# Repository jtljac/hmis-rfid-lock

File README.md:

# hmis-locks
A [PlatformIO](https://platformio.org/) program for a electronic locks that are unlocked using a Wiegand based RFID 
scanner and authorises users using a HMIS endpoint.

# Keypad support
Wiegand readers with keypads are supported. You can configure the valid keycode by setting the `enable_keypad_passcode`
option to a numeric string up to 8 numbers long.

When using the keypad, the '*' (star) button will clear (provided it maps to 0x0A), and the '#' (Hashtag) button will
submit (provided it maps to 0x0B).

# Setup
## Platform IO
This application uses [PlatformIO](https://platformio.org/) for dependency management and installation. Installation
instructions for your platform can be found [here](https://platformio.org/install/cli).

## Config
Configuration options have been exposed in [platformio.ini](/platformio.ini) under the `[base_config]` section.

The `WiFi` and `HMIS` options must be configured for your network and HMIS server. 

The `Unlock` and `Auth` options can be configured to suit your needs. 

The `Pins` options should be configured for your ESP, preferably in a separate section that inherits the `[base_config]` 
section (see the `[config_dfrobot_firebeetle2_esp32e]` section for an example of this).

The `Pin Inversions` options should be configured to match your circuit.

A preset environment has been provided for the [FireBeetle 2 ESP32-E](https://wiki.dfrobot.com/FireBeetle_Board_ESP32_E_SKU_DFR0654#target_5)
(my chosen ESP32), you will need to provide your own environment with it's required pin setup if you have a different
ESP32 (we welcome PRs for alternative setups).

## Installation
Run the following to build and upload the project to your ESP32:
```shell
# [your-env] should be one of the configured env sections in platformio.ini
pio run -t upload -e [your-env]
```

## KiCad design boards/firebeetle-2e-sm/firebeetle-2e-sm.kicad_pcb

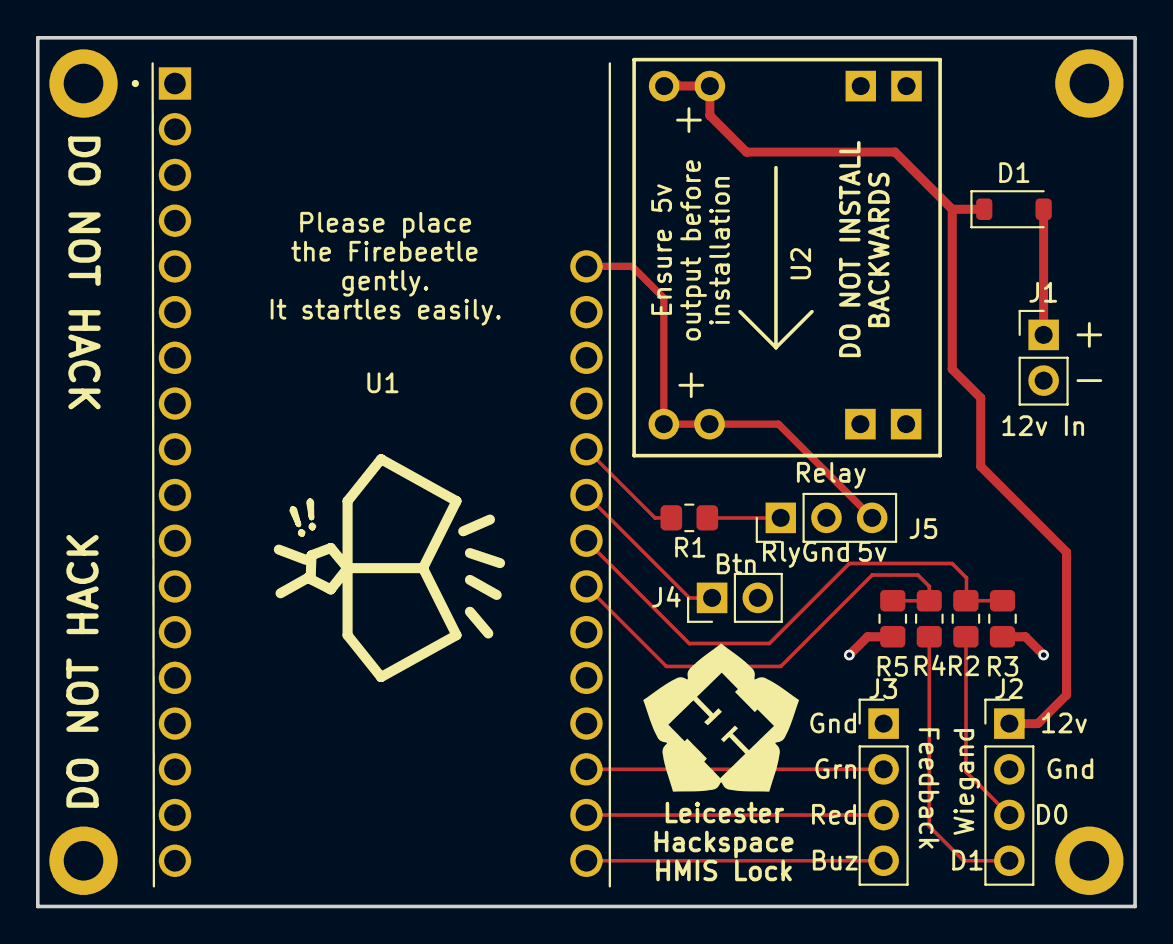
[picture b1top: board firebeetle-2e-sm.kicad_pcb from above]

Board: 2 copper layers, 61.0 x 48.3 mm, 17 parts (0 on the bottom side), 14 nets.

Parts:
D1: 1N5819; D_SOD-123
J1: Power In; PinHeader_1x02_P2.54mm_Vertical
J2: Wiegand; PinHeader_1x04_P2.54mm_Vertical
J3: Feedback; PinHeader_1x04_P2.54mm_Vertical
J4: Button; PinHeader_1x02_P2.54mm_Vertical
J5: Relay; PinHeader_1x03_P2.54mm_Vertical
M1, M2, M3, M4: MountingHole_2.2mm_M2_DIN965_Pad
R1: 5k1; R_0805_2012Metric_Pad1.20x1.40mm_HandSolder
R2, R4: 1k; R_0805_2012Metric_Pad1.20x1.40mm_HandSolder
R3, R5: 3.3k; R_0805_2012Metric_Pad1.20x1.40mm_HandSolder
U1: DFR0654; MODULE_DFR0654
U2: MP1584EN Module

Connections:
+5V: J5.3, U1.5 (VCC), U2.4 (VOut)
+12V: D1.1 (K), J2.1, U2.1 (VIn)
/Btn: J4.1, U1.15 (A4)
/Relay: R1.1, U1.21 (SDA)
/buz: J3.4, U1.17 (D10)
/d0: R2.1, R3.2, U1.35 (A3)
/d1: R4.1, R5.1, U1.34 (A2)
/grn: J3.2, U1.4 (D12)
/red: J3.3, U1.16 (D11)
GND: J1.2, J2.2, J3.1, J4.2, J5.2, M1.1, M2.1, M3.1, M4.1, R3.1, R5.2, U1.7 (GND), U2.2 (Gnd), U2.3 (Gnd)
unnamed: D1.2 (A), J1.1
unnamed: J2.3, R2.2
unnamed: J2.4, R4.2
unnamed: J5.1, R1.2

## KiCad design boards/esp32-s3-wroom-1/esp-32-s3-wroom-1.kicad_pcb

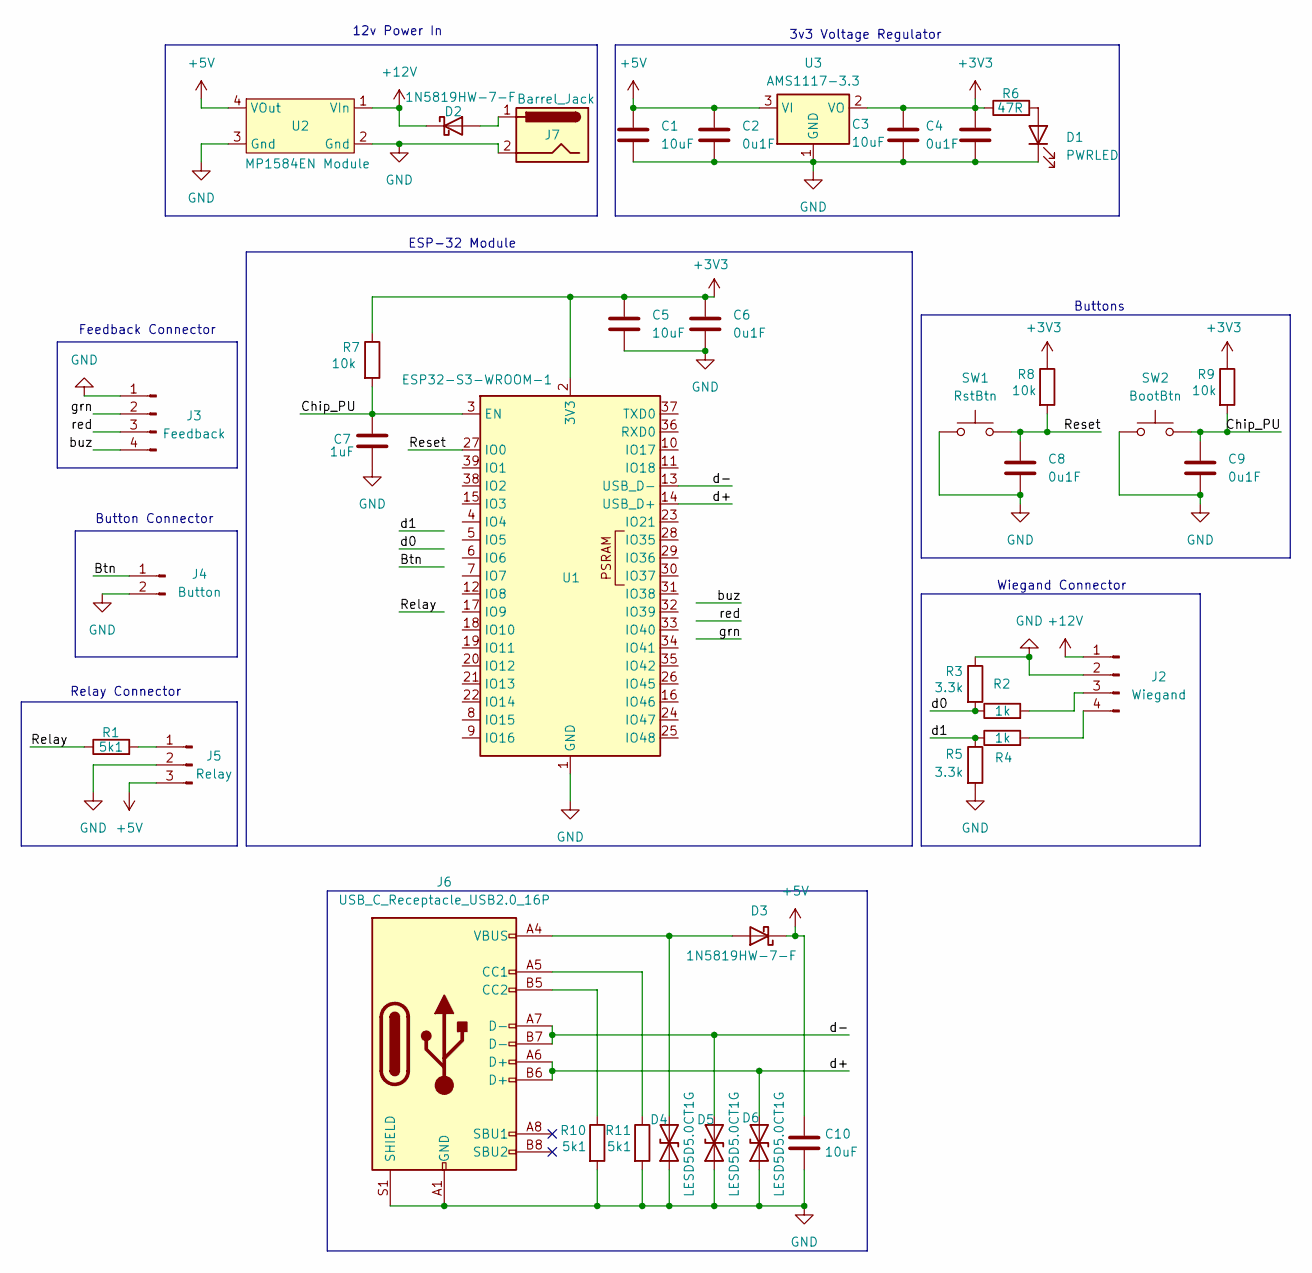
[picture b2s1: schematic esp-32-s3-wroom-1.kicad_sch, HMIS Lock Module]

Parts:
C1, C3, C5, C10: 10uF; C_0805_2012Metric
C2, C4, C6, C8, C9: 0u1F; C_0805_2012Metric
C7: 1uF; C_0805_2012Metric
D1: PWRLED; LED_0603_1608Metric
D2, D3: 1N5819HW-7-F; D_SOD-123
D4, D5, D6: LESD5D5.0CT1G; D_SOD-523
J2: Wiegand; PinHeader_1x04_P2.54mm_Vertical
J3: Feedback; PinHeader_1x04_P2.54mm_Vertical
J4: Button; PinHeader_1x02_P2.54mm_Vertical
J5: Relay; PinHeader_1x03_P2.54mm_Vertical
J6: USB_C_Receptacle_USB2.0_16P; USB_C_Receptacle_GCT_USB4105-xx-A_16P_TopMnt_Horizontal
J7: Barrel_Jack; BarrelJack_CUI_PJ-102AH_Horizontal
R1, R10, R11: 5k1; R_0805_2012Metric
R2, R4: 1k; R_0805_2012Metric
R3, R5: 3.3k; R_0805_2012Metric
R6: 47R; R_0805_2012Metric
R7, R8, R9: 10k; R_0805_2012Metric
SW1: RstBtn; SW-SMD_L4.0-W2.9-LS5.0
SW2: BootBtn; SW-SMD_L4.0-W2.9-LS5.0
U1: ESP32-S3-WROOM-1
U2: MP1584EN Module
U3: AMS1117-3.3; SOT-223-3_TabPin2

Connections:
+3V3: C3.1, C4.1, C5.1, C6.1, R6.1, R7.1, R8.1, R9.1, U1.2 (3V3), U3.2 (VO)
+5V: C1.1, C2.1, C10.1, D3.1 (K), J5.3, U2.4 (VOut), U3.3 (VI)
+12V: D2.1 (K), J2.1, U2.1 (VIn)
/Btn: J4.1
/Chip_PU: C7.1, C9.1, R7.2, R9.2, SW2.2, U1.3 (EN)
/Relay: R1.1
/Reset: C8.1, R8.2, SW1.2, U1.27 (IO0)
/buz: J3.4
/d0: R2.1, R3.2
/d1: R4.1, R5.1
/d+: D6.2 (A2), J6.A6 (D+), J6.B6 (D+), U1.14 (USB_D+)
/d-: D5.2 (A2), J6.A7 (D-), J6.B7 (D-), U1.13 (USB_D-)
/grn: J3.2
/red: J3.3
GND: C1.2, C2.2, C3.2, C4.2, C5.2, C6.2, C7.2, C8.2, C9.2, C10.2, D1.1 (K), D4.1 (A1), D5.1 (A1), D6.1 (A1), J2.2, J3.1, J4.2, J5.2, J6.A1 (GND), J6.A12 (GND), J6.B1 (GND), J6.B12 (GND), J6.S1 (SHIELD), J7.2, R3.1, R5.2, R10.2, R11.2, SW1.1, SW2.1, U1.1 (GND), U1.40 (GND), U1.41 (GND), U2.2 (Gnd), U2.3 (Gnd), U3.1 (GND)
unnamed: D1.2 (A), R6.2
unnamed: D2.2 (A), J7.1
unnamed: D3.2 (A), D4.2 (A2), J6.A4 (VBUS), J6.A9 (VBUS), J6.B4 (VBUS), J6.B9 (VBUS)
unnamed: J2.3, R2.2
unnamed: J2.4, R4.2
unnamed: J5.1, R1.2
unnamed: J6.A5 (CC1), R11.1
unnamed: J6.B5 (CC2), R10.1

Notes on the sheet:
Relay Connector
Wiegand Connector
Feedback Connector
ESP-32 Module
3v3 Voltage Regulator
Buttons
12v Power In
Button Connector

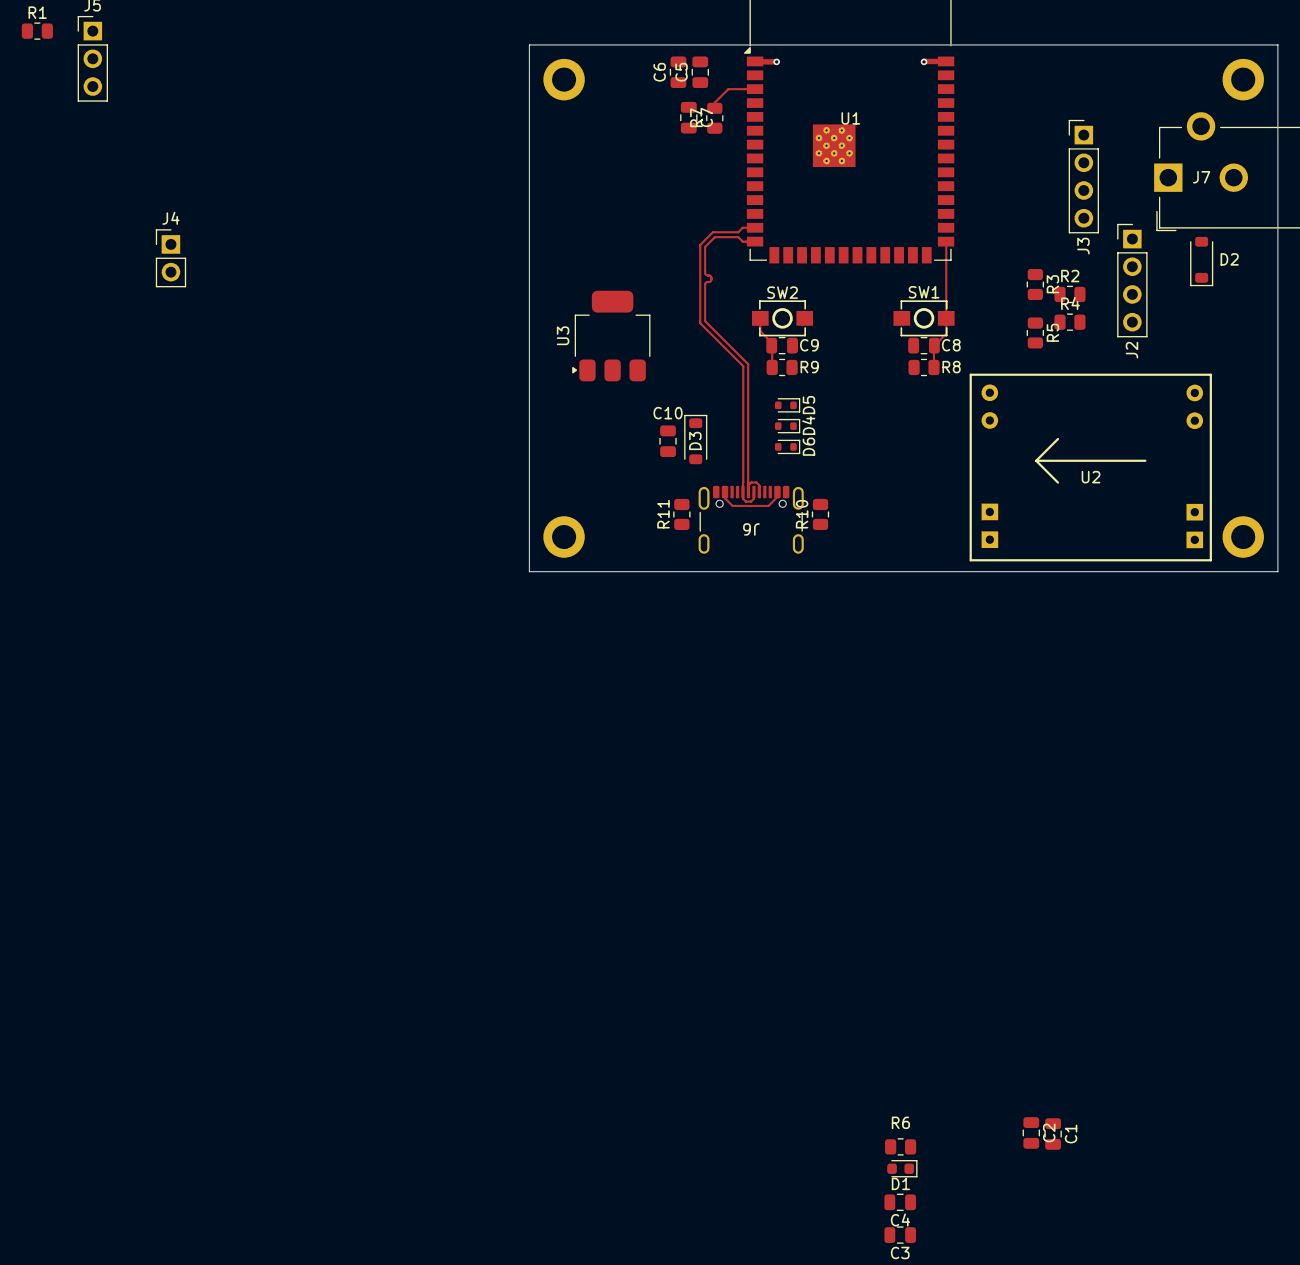
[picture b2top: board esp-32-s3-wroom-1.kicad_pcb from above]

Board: 2 copper layers, 68.6 x 48.3 mm, 38 parts (0 on the bottom side), 18 nets.

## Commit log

2024-04-28 Terminal Added classes for handling feedback, implemented class for handling the lock, moved RFID handling into own class
    Feedback includes LEDs, buzzers
2024-04-28 Cleanup, documentation, add unlock on correctly scanned keycard
2024-04-29 Added animations to Output class, fixed incorrect usage of lock and unlock outputs, added flash and tone on failed login
2024-04-29 Handle when output changes during an animation, and when a key is scanned whilst currently unlocked
2024-04-29 Fix state, cleanup
2024-04-29 Add option to check auth with live endpoint, fixed card scanned during unlock being checked after locking
2024-04-29 Improve platformio ini file, improved documentation, changed relay to use output
    Added pin configs that are setup per board in platformio.ini,
    Added URL to platformIO ini,
2024-04-29 Removed json and stream utils libraries
2024-04-29 Added inversion options, patched http requests not ending
2024-04-30 Fix bug where lapse in D1 and D0 communication caused panic
2024-04-30 Add Readme and license
2024-05-02 Added configuration for entering a keycode
2024-05-06 Changed default firebeetle pins, disabled keypad by default, removed extra log
2024-05-06 Added a configurable delay after failing authorisation to slow brute force attacks
2024-05-13 Updated firebeetle pin layout, added board design for firebeetle
2024-05-15 Fixed misbehaving firebeetle pins, adjusted firebeetle board for new pins
2024-05-23 Modified board, added pullup setting to button pins, changed http 200 to constant
2024-08-14 Add OTA support
2024-08-17 Fixed comments, moved wifi out of class handling auth
2024-09-13 Updated Board design for Firebeetle
2025-01-05 Implemented new board, with proper schematic this time
    Went back to voltage divider as the 5v rail from the wiegand wasn't available, nd the protocol is one way anyway
2025-01-07 Fixed issues with firebeetle board
2025-01-21 Updated firebeetle design
2025-01-21 Started raw ESP32-s3-wroom design
2025-01-31 Continued work on raw esp
2025-02-22 Firebeetle EEs
2025-02-26 Created separate through hole and surface mount designs for firebeetle
2025-03-06 Addressed design rules for firebeetle surface mount
2025-03-06 continued work
2025-03-21 Added ability to use the button to unlock
2025-03-23 Added 10uF capacitor between reset and ground to handle slow power supply
2025-03-24 Revert EN capacitor, update firebeetle th, updated documentation to remove MP2307EN SS capacitor
2026-04-12 Added ability to add delay to button press until it triggers the lock
2026-05-20 Add buzzer noise on lock when unlock buzz is disabled
2026-05-30 Use High impedance for locked instead of high or low
